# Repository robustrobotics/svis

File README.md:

# svis
This is a meta-project that contains all of the components that create a Simple Visual Inertial Synchronization approach.  The components are defined as follows.

- svis: The core algorithmic C++ library that matches camera strobe messages to camera images and gives them a common time based on the teensy clock.
- svis_ros: The ROS wrapper C++ library that handles the input and output from the core svis library.
- svis_teensy: The C and C++ code, dependencies, and utilities that build the teensy driver and allow it to be uploaded to the board.
- svis_cad: The solidworks CAD files for the svis mounting structure.
- svis_pcb: The Eagle PCB files for the svis circuit board.

### Dependencies
A list of noteable dependencies can be found below.
- catkin_tools
- Ubuntu 16.04
- ROS Kinetic
- ros-kinetic-pointgrey-camera-driver
- libusb-dev
- flycapture SDK

Use the following commands to install the required apt dependencies.
```
sudo apt install python-catkin-tools
sudo apt install ros-kinetic-pointgrey-camera-driver
sudo apt install libusb-dev
sudo apt install libc6-i386
```

Add user to dialout group.
```
sudo adduser $USER dialout
```

Use the following commands to install the flycapture SDK.
```
cd /path/to/svis/svis_ros/scripts
./install_flycapture.sh
```
Installation Steps:
- Enter sudo password: ["password", Enter]
- Confirm apt package installation: [Enter]
- Install FlyCapture2 SDK: [y, Enter]
- Add udev entry: [y, Enter]
- Enter username: ["username", Enter]
- Confirm username: [y, Enter]
- Add username to flirimaging group: [y, Enter]
- Restart udev daemon: [y, Enter] 

### Quick Start
The rough outline for running svis is as follows.  More details can be found in the individual package README files.
- Build svis and svis_ros code.
```
mkdir -p /path/to/catkin_ws/src
cd /path/to/catkin_ws/src
git clone http://github.com/jakeware/svis
cd ../
source /opt/ros/kinetic/setup.bash
catkin init
catkin config --cmake-args -DCMAKE_BUILD_TYPE=Release
catkin build
```
- Build svis_teensy code.
```
cd ./path/to/svis/svis_teensy/scripts
./build_svis_teensy.sh
```
- Install the udev rules for the teensy.
```
sudo cp /path/to/svis/svis_teensy/utilities/49-teensy.rules /etc/udev/rules.d/
```
- Upload teensy driver.  Make sure the teensy's micro USB cable is connected.  When prompted, press the program button on the teensy.
```
cd ./path/to/svis/svis_teensy/scripts
./upload_svis_teensy.sh
```
- Start the Pointgrey camera driver.
```
cd /path/to/catkin_ws
source ./devel/setup.bash
roslaunch svis_ros flea3.launch
```
- Start the svis_ros nodelet.
```
cd /path/to/catkin_ws
source ./devel/setup.bash
roslaunch svis_ros svis_ros_nodelet.launch
```

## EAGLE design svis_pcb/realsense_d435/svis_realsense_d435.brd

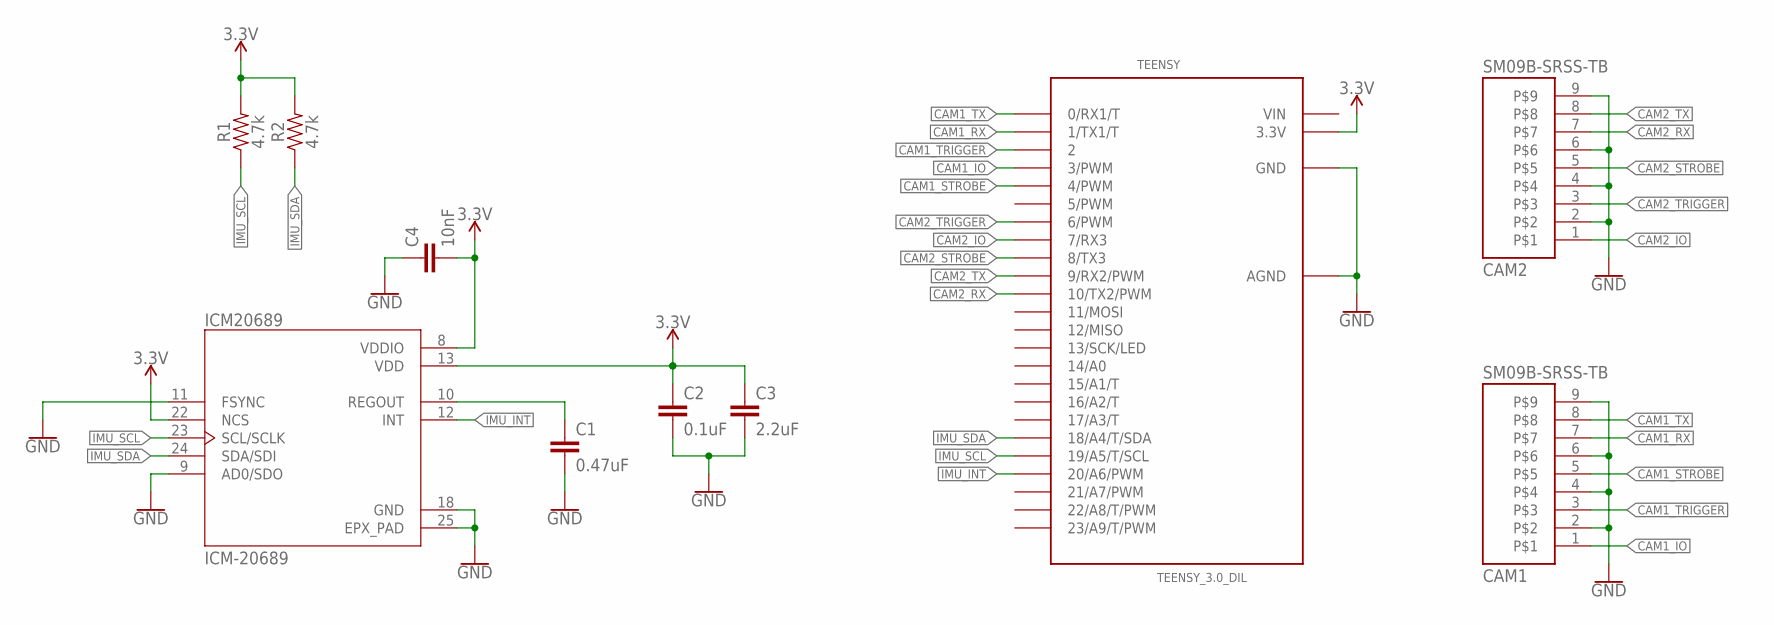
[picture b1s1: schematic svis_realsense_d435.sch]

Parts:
C1: 0.47uF; 0603
C2: 0.1uF; 0603
C3: 2.2uF; 0603
C4: 10nF; 0603
CAM1, CAM2: SM09B-SRSS-TB
ICM20689: ICM-20689; QFN50P400X400X95-25N
R1, R2: 4.7k; 0603
TEENSY: TEENSY_3.0_DIL; TEENSY_3.0-3.2&LC_DIL

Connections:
3.3V: C2.1, C3.1, C4.2, ICM20689.8 (VDDIO), ICM20689.13 (VDD), ICM20689.22 (NCS), R1.2, R2.2, TEENSY.3.3V
CAM1_IO: CAM1.1, TEENSY.3 (3/PWM)
CAM1_RX: CAM1.7, TEENSY.1 (1/TX1/T)
CAM1_STROBE: CAM1.5, TEENSY.4 (4/PWM)
CAM1_TRIGGER: CAM1.3, TEENSY.2
CAM1_TX: CAM1.8, TEENSY.0 (0/RX1/T)
CAM2_IO: CAM2.1, TEENSY.7 (7/RX3)
CAM2_RX: CAM2.7, TEENSY.10 (10/TX2/PWM)
CAM2_STROBE: CAM2.5, TEENSY.8 (8/TX3)
CAM2_TRIGGER: CAM2.3, TEENSY.6 (6/PWM)
CAM2_TX: CAM2.8, TEENSY.9 (9/RX2/PWM)
GND: C1.2, C2.2, C3.2, C4.1, CAM1.2, CAM1.4, CAM1.6, CAM1.9, CAM2.2, CAM2.4, CAM2.6, CAM2.9, ICM20689.9 (AD0/SDO), ICM20689.11 (FSYNC), ICM20689.18 (GND), ICM20689.25 (EPX_PAD), TEENSY.AGND, TEENSY.GND
IMU_INT: ICM20689.12 (INT), TEENSY.20/A6 (20/A6/PWM)
IMU_SCL: ICM20689.23 (SCL/SCLK), R1.1, TEENSY.19/A5 (19/A5/T/SCL)
IMU_SDA: ICM20689.24 (SDA/SDI), R2.1, TEENSY.18/A4 (18/A4/T/SDA)
unnamed: C1.1, ICM20689.10 (REGOUT)
VIN: TEENSY.VIN

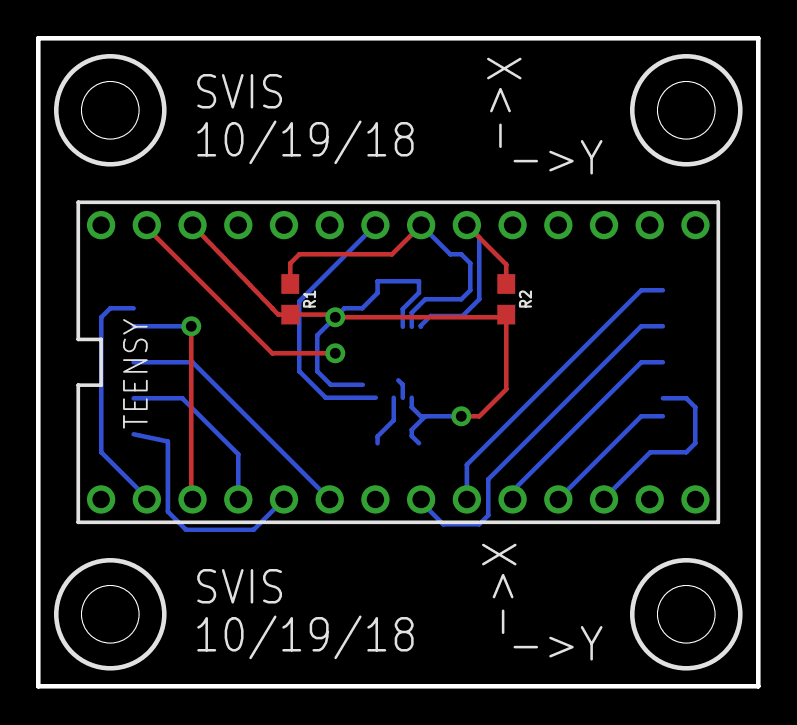
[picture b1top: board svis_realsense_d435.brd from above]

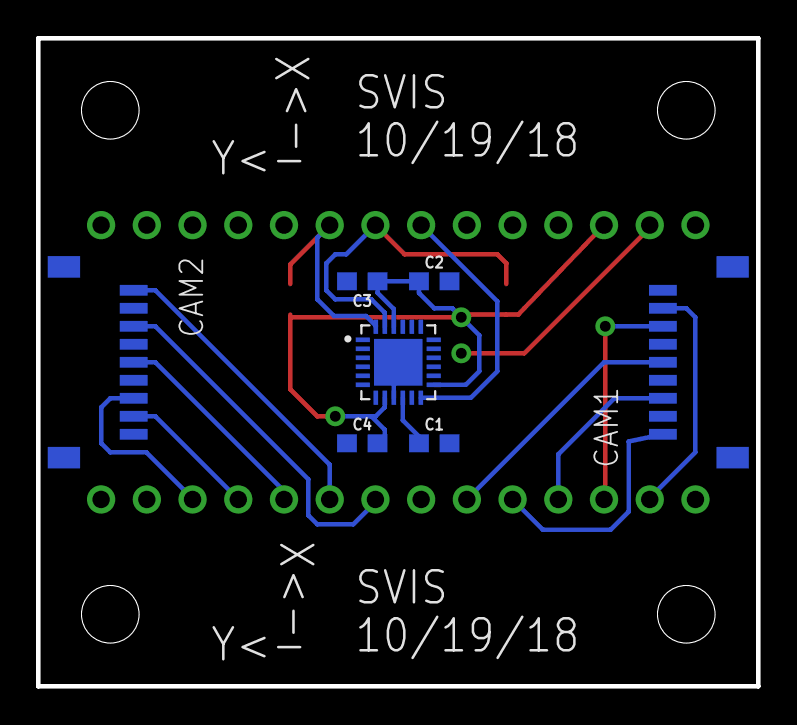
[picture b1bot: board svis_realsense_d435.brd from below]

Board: 2 copper layers, 40.0 x 36.0 mm, 10 parts (7 on the bottom side), 16 nets.

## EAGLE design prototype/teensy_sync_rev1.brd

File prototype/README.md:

# svis_cad_prototype
This package contains the CAD portion of a Simple Visual Inertial
Synchronization approach.  Due to the size of CAD files, this portion of the
project is maintained in OnShape.

* [svis_cad_prototype_mono](https://cad.onshape.com/documents/99ae2ad9c7ddd392e4e0b58d/w/969cc026d4e8d11d2a2540fa/e/534a900b9d68d548818dfd7e)
* [svis_cad_prototype_stereo](https://cad.onshape.com/documents/c2e3b5391432601dd5a34811/w/07971ed09aed7bb4962e395a/e/211f444c45c3098888544dae)

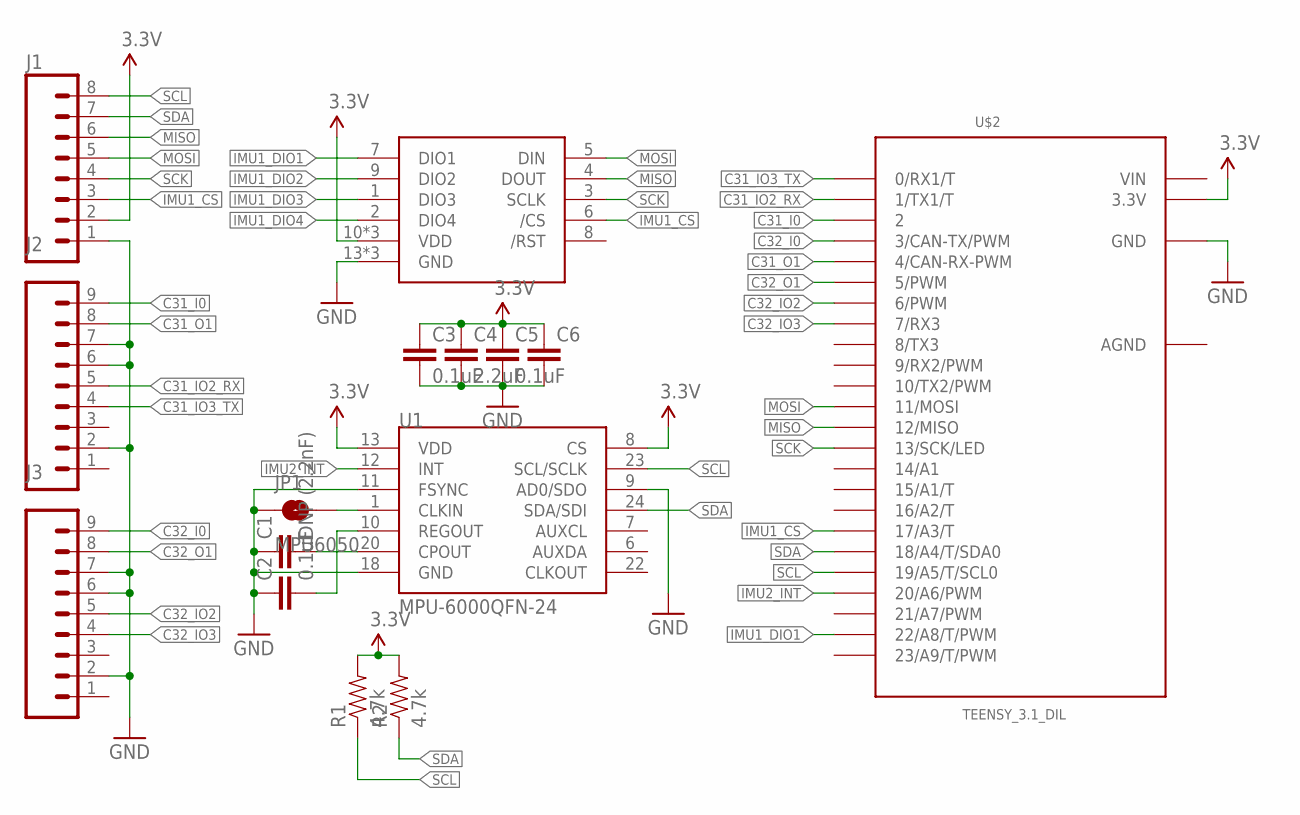
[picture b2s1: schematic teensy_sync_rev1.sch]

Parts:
C1: DNP (2.2nF); 0402-CAP
C2, C3, C5: 0.1uF; 0402-CAP
C4: 2.2uF; 0402-CAP
C6: CAP0402-CAP; 0402-CAP
J1: M08; 1X08_ROUND
J2, J3: M09; 1X09
JP1: MPU6050; PAD-JUMPER-2-NO_YES_SILK
R1, R2: 4.7k; 0603-RES
U1: MPU-6000QFN-24; QFN-24-TESTING
U$1: ADIS16448
U$2: TEENSY_3.1_DIL; TEENSY3-DIL

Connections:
3.3V: C3.1, C4.1, C5.1, C6.1, J1.2, R1.2, R2.2, U1.8 (CS), U1.13 (VDD), U$1.10 (VDD), U$1.11 (VDD), U$1.12 (VDD), U$2.3.3V
AGND: U$2.AGND
C31_I0: J2.9, U$2.2
C31_IO2_RX: J2.5, U$2.1 (1/TX1/T)
C31_IO3_TX: J2.4, U$2.0 (0/RX1/T)
C31_O1: J2.8, U$2.4 (4/CAN-RX-PWM)
C32_I0: J3.9, U$2.3 (3/CAN-TX/PWM)
C32_IO2: J3.5, U$2.6 (6/PWM)
C32_IO3: J3.4, U$2.7 (7/RX3)
C32_O1: J3.8, U$2.5 (5/PWM)
GND: C1.1, C2.1, C3.2, C4.2, C5.2, C6.2, J1.1, J2.2, J2.6, J2.7, J3.2, J3.6, J3.7, JP1.1, U1.9 (AD0/SDO), U1.11 (FSYNC), U1.18 (GND), U$1.13 (GND), U$1.14 (GND), U$1.15 (GND), U$2.GND
IMU1_CS: J1.3, U$1.6 (/CS), U$2.17/A3 (17/A3/T)
IMU1_DIO1: U$1.7 (DIO1), U$2.22/A8 (22/A8/T/PWM)
IMU1_DIO2: U$1.9 (DIO2)
IMU1_DIO3: U$1.1 (DIO3)
IMU1_DIO4: U$1.2 (DIO4)
IMU2_INT: U1.12 (INT), U$2.20/A6 (20/A6/PWM)
MISO: J1.6, U$1.4 (DOUT), U$2.12 (12/MISO)
MOSI: J1.5, U$1.5 (DIN), U$2.11 (11/MOSI)
unnamed: C1.2, U1.20 (CPOUT)
unnamed: JP1.2, U1.1 (CLKIN)
REGOUT: C2.2, U1.10 (REGOUT)
SCK: J1.4, U$1.3 (SCLK), U$2.13 (13/SCK/LED)
SCL: J1.8, R1.1, U1.23 (SCL/SCLK), U$2.19/A5 (19/A5/T/SCL0)
SDA: J1.7, R2.1, U1.24 (SDA/SDI), U$2.18/A4 (18/A4/T/SDA0)
VIN: U$2.VIN

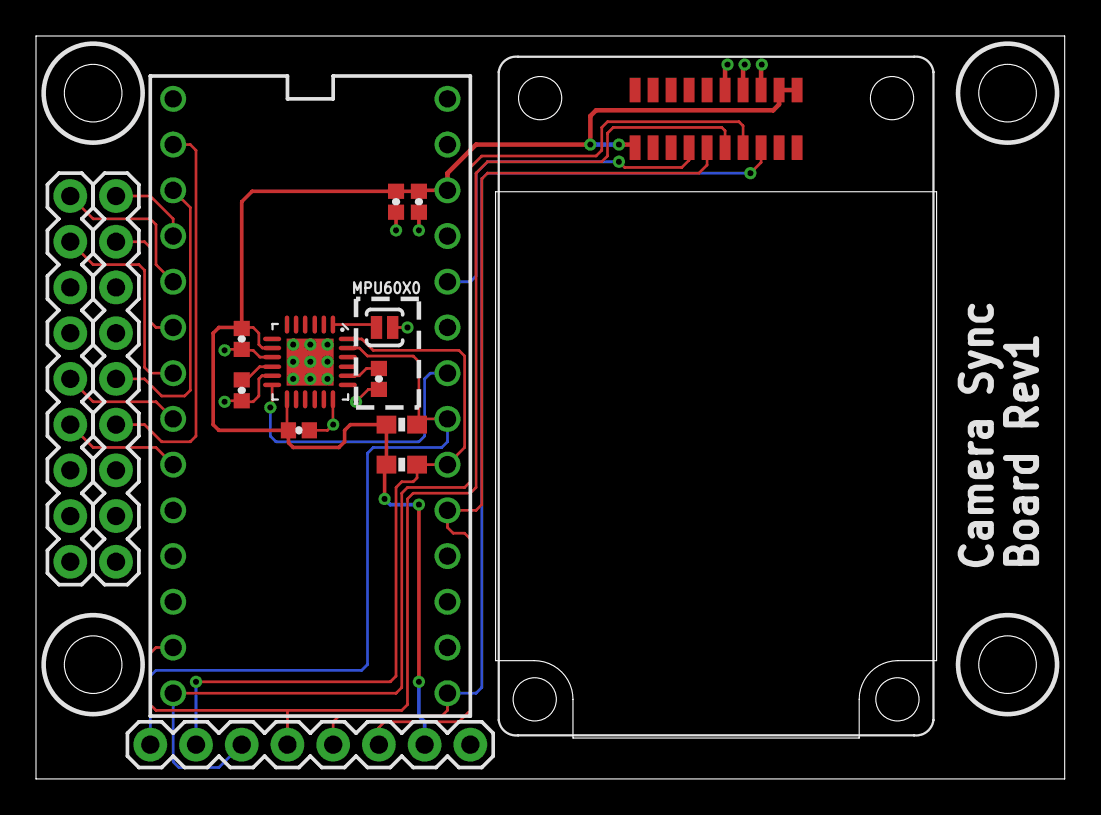
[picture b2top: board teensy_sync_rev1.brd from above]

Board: 2 copper layers, 57.1 x 41.3 mm, 15 parts (0 on the bottom side), 21 nets.

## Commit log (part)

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2016-12-23 Switch upload command to CLI.
2016-12-23 Remove ARDUINO_HOME.
2016-12-23 Remove TEENSY3_OVERRIDE_FILES.
2016-12-23 Add comment blocks for separation.
2016-12-23 Remove M_LAYOUT.
2016-12-23 Remove check for linker definitions override.
2016-12-23 Remove M_TEENSY_VERSION and M_BOARD.
2016-12-23 Move PROJECT_PATH variable.
2016-12-23 Remove unused make targets.
2016-12-23 Change OUT_PATH to BIN_PATH.
2016-12-23 Add build folder.
2016-12-23 Remove LICENSE.txt.
2016-12-23 Move bin into build folder.
2016-12-23 Remove original blink example.
2016-12-23 Rename and cleanup new blink example.
2016-12-23 Rename blink project target.
2016-12-24 Working hello_world example.
2016-12-24 Update usb_raw_hid structure.
2016-12-24 Add cores folder and move teensy3.
2016-12-24 Add missing cores folders
2016-12-24 Remove usb libraries in tools.
2016-12-24 Rename tools to utilities.
2016-12-25 Reworking blink. Currently broken.
2016-12-25 Add initial cmake files.
2016-12-26 Comment out CMAKE_TOOLCHAIN_FILE.
    This variable does not exist in cmake 2.8.
2016-12-26 Switch TOOLCHAIN_ROOT to TOOLCHAIN_PREFIX.
2016-12-26 Remove TOOL_OS_SUFFIX.
2016-12-26 Update paths and variables.
2016-12-26 Remove unnecessary quotes from definitions.
2016-12-26 Remove CACHE STRING and comment.
2016-12-26 Unset CMAKE_SHARED_LIBRARY_LINK variables.
2016-12-26 Remove debugging work.
2016-12-26 Cleanup CMakeLists.
2016-12-26 Remove redundant mk20dx256.ld.
2016-12-26 Update TEENSYDUINO_VERSION in blink Makefile.
2016-12-26 Remove usb dependency files accidentally added in previous commit.
2016-12-27 Remove examples CMakeLists.
2016-12-27 Add TODO for cmake includes.
2016-12-27 Remove TyQt references.
2016-12-27 Use GLOB for teensy core.
2016-12-27 Add prints for blink Makefile build.
2016-12-27 Update compile and link flags.
2016-12-27 Remove Blink.pde.
2016-12-28 Remove usb_api.h from usb_raw_hid example.
2016-12-28 Remove blink Makefile.
2016-12-28 Remove usb_raw_hid Makefile.
2016-12-28 Add project specific CMakeLists files.
2016-12-28 Set TEENSY_FREQUENCY to 48MHz.
2016-12-28 Switch to using project specific CMakeLists.
2016-12-28 Fix C_CORE GLOB typo.
2016-12-28 Remove USB_MODE and FREQUENCY from default defs.
2016-12-28 Remove empty CMakeLists.
2016-12-28 Move everything up a level for svis_teensy change.
2016-12-30 Rough README.
2016-12-30 Add partial code to automatically parse version numbers.
2016-12-31 Add attach_interrupt example.
2017-01-01 Add adafruit_9dof example.
2017-01-07 Add MPU6050 library.
2017-01-07 Add mpu6050_raw example.
2017-01-19 Initial working IMU callbacks.
2017-01-19 Single imu read function at 1kHz.
2017-01-19 Cleanup.
2017-01-19 Rough out strobe and imu implementation.
2017-01-20 Decrease imu interrupt for debugging.
2017-01-20 Switch back to SERIAL for debugging.
2017-01-20 Comment out HID send.
2017-01-20 Add checks for count and tail.
2017-01-20 Cleanup setup function.
2017-01-20 Add led blink and cleanup.
2017-01-20 Modify blinking.
2017-01-20 Add debug prints and PrintSendBuffer..
2017-01-20 Add strobe_count and cleanup.
2017-01-20 Remove debug prints.
2017-01-21 Add initial files.
2017-01-21 Add initial hid files.
2017-01-21 Remove hid Makefile.
2017-01-21 Rename hid_LINUX.c.
2017-01-21 Cleanup and rename.
2017-01-21 Initial launch file.
2017-01-22 Fixed usb linking error.
2017-01-22 Switch to RAWHID.
2017-01-22 Remove rawhid send prints.
2017-01-22 Add packet counts.
2017-01-22 Disable CMAKE_VERBOSE_MAKEFILE.
2017-01-22 Add #defines for sizes.
2017-01-23 Refactor to use fixed packet structure.
2017-01-23 Initial refactor to use fixed packet structure.
2017-01-23 Add checksum and replace defines with constants.
2017-01-23 Partial cleanup.
2017-01-23 Added initial version of board schematic and layout.
2017-01-23 Add send_errors.
2017-01-24 Move struct definitions.
2017-01-24 Switch to std::vector for buffer.
2017-01-24 Add TestPushIMU and TestPushStrobe.
2017-01-24 Fix imu_data_buffer indexing.
2017-01-24 Added ICM20689.h to replace MPU6050.h
2017-01-24 Remove unused files.
2017-01-24 Copy MPU6050 for base of ICM20689.
2017-01-24 Updated library.json to ICM20689 version. Modified from MPU6050 version.
2017-01-24 Cleaned up ICM20689.h. Commented out any unimplemented functions for first test.
2017-01-25 Updated brd and sch file to reflect prototype boards ordered.
2017-01-25 Add image callback and debug.
2017-01-25 Added BOM for prototype PCB.
2017-01-26 Add debug messages.
2017-01-26 Add imu low-pass filter.
2017-01-31 White space cleanup.
2017-01-31 Add path to hid.h include.
2017-01-31 Remove dt print statement.
2017-01-31 Start rough time offset implementation.
2017-02-01 Update struct names.
2017-02-02 Rework timestamps.
2017-02-02 Fix time_offset calculation and variable types.
2017-02-02 Do not force strobe_count rollover.
2017-02-02 Rename image pub and sub.
2017-02-02 Add raw strobe and imu ros messages for debug.
2017-02-02 Define STROBE_PIN and add INPUT_PULLUP option.
    Not that the pullup resistor on the teensy is too high to be useful.
2017-02-02 Switch from RISING to FALLING on strobe interrupt.
    This is to match the default ROS driver configuration.
2017-02-02 Change print statement for no data case.
2017-02-02 Add raw publishers and Push functions.
2017-02-02 Add ImageMetadata class.
2017-02-03 Add rough sync function.
2017-02-03 Cleanup and add GetCountOffset().
2017-02-03 Organize member variables.
2017-02-03 Cleanup and initialize all member variables.
2017-02-04 Move spinOnce() to top of loop.
2017-02-04 Fix strobe_count_total bug.
2017-02-04 Add iterator loops to AssociateStrobe.
    Also remove strobe and camera packets once matched.
2017-02-04 Dirty hack to get around ConstPtr camera message.
    Couldn't figure out a way to modify the timestamp on the ConstPtr
    messages Image and CameraInfo messages.
2017-02-06 Add Image callback. Currently segfaulting.
2017-02-06 Debugging...
2017-02-07 Add PrintStrobeBuffer.
2017-02-07 Rollover fix. Fuck that. Seriously.
2017-02-07 Add raw strobe count to PrintStrobeBuffer.
2017-02-07 Add timing.
2017-02-07 Copy camera image and info message.
2017-02-07 Cleanup print statements.
2017-02-07 Add links to prototype files.
2017-02-07 Add initial versions of repos.
2017-02-08 Switch to ICM20689.
2017-02-08 Fix mpu6050/icm20689 mixup.
2017-02-09 Fix trigger timing.
2017-02-09 Add configuration packet and startup led blinks.
2017-02-09 Add configuration packet.
2017-02-09 Remove ros submodule.
2017-02-09 Remove pcb submodule.
2017-02-09 Remove svis prefix from folders.
2017-02-09 Add warning for missing camera messages.
2017-02-09 Reorganize GetStrobeTotal.
2017-02-09 Add reset function.
2017-02-09 Update led user feedback blink functions.
2017-02-09 Fix setup header typo.
2017-02-09 Cleanup SIGINT warning text.
2017-02-10 Add SendSetup().
2017-02-10 Add warnings when buffers are at max size.
2017-02-10 Comment out rollover warning.
2017-02-13 Correct param yaml name.
2017-02-14 Cleanup launch file comments.
2017-02-14 Move params out of node to fix namespace issue.
2017-02-14 Add acc and gyro sensitivity params.
2017-02-14 Rearrange teensy blink functions.
2017-02-14 Add ResetParams function.
2017-02-14 Move gyro and acc range select assignment.
2017-02-14 Add accel and gyro range select and correction to ros.
2017-02-14 Convert accelerations into m/s.
2017-02-14 Fix AFS_SEL reference table.
2017-02-14 Move param load to fix namespace issue again.
2017-02-28 Revert lp_win_size to imu_filter_size.
2017-02-28 Add rad_per_deg constant.
2017-02-28 Add acc_raw and gyro_raw variables to ImuPacket.
2017-02-28 Publish converted Imu messages.
2017-02-28 Switch to static_cast.
2017-02-28 Fix gyro and accel range comment.
2017-02-28 Switch loops to use size() for max value.
2017-02-28 Update FilterImu to use floats and new format.
2017-02-28 Add check for camera trigger reconfigure step.
2017-02-28 Add dynamic_reconfigure step for camera trigger.
2017-03-01 Make camera_frame an arg.
2017-07-07 Add udev rules.
2017-07-07 Reduce camera rate to 30 Hz to avoid rate bug.
2017-07-07 Add camera driver warning.
2017-07-07 Switch to using camera and strobe pairs.
2017-07-07 Formatting.
2017-07-07 Add trigger pulse packets.
    Builds but is still untested.
2017-07-07 Add buffer size prints.
2017-07-07 Fix buffer size bug.
2017-08-30 Move data structs and classes into their own headers.
2017-08-30 Move implementation from nodelet into ros wrapper.
2017-08-30 Move data structs and classes to svis.
2017-08-31 Add svis library and start refactor.
2017-08-31 Add svis object back into svis_ros.
2017-08-31 Cleanup timing stuff.
2017-08-31 Pass buffers to Push functions.
2017-08-31 Cleanup Update function.
2017-08-31 Add constructor.
2017-08-31 Always pass buffers.
2017-08-31 Add num return to ReadHID.
2017-08-31 Timing cleanup and add private members to svis.
2017-08-31 More timing cleanup.
2017-08-31 Add PublishTiming place holder.
2017-08-31 Add new lines to printf statements.
2017-09-04 Remove svis_ros dependency of svis_ros_nodelet.
2017-09-04 Remove public declaration in CameraStrobePacket struct.
2017-09-05 Switch to std::size_t.
2017-09-05 Reorganize headers.
2017-09-05 Make publishers const, except for camera pub.
2017-09-06 Add custom messages.
2017-09-06 Add semicolon after struct definitions.
2017-09-06 Fix timestamp_ros_rx initialization typo.
2017-09-06 Switch to std::memcpy.
2017-09-06 Comment out PrintImageQuadlet and PrintMetaDataRaw.
2017-09-06 Add svis_ros back to nodelet dependency.
    Removing this caused runtime errors with undefined symbols.
2017-09-06 Add msg conversion functions.
2017-09-06 Switch to std::array in camera_info.h.
2017-09-06 Add TimeNow std::function to svis.
2017-09-06 Remove stamp struct from header and switch to double.
2017-09-07 Remove svis from ros wrapper build and add as cmake dependency.
2017-09-07 Add svis cmake library.
2017-09-07 Rename folders.
2017-09-08 Fixed libusb build issue. Includes extra debugging code.
2017-09-10 Hardcode svis library path. This works.
2017-09-11 Remove svis_INCLUDE_DIRS and svis_LIBRARIES prints.
2017-09-11 Remove unnecessary compile and linker flags.
2017-09-11 Cleanup cmake.in.
2017-09-11 Fix sloppy memory leak.
2017-09-12 Set pulse_trigger on restart. Seems to work now.
2017-09-14 Add CMSIS DSP math library.
2017-09-14 Upload documentation and cleanup cmake.
2017-09-14 Remove .gitmodules file.
2017-09-19 Cleanup README.
2017-09-19 Update README.
2017-09-19 Uncomment gcc-arm wget.
2017-09-22 First round of build fixes.
2017-09-29 Add install_flycapture script.
2017-10-14 Update shutter speed and add flea3 calibration.
2018-07-03 Add libc6-i386 dependency.
2018-07-03 Add user to dialout.
2018-07-05 Do not cast timestamp_teensy as an int after averaging.
2018-07-06 Add DecimateImu.
2018-07-06 Add artificial time offset.
2018-07-09 Fix circular buffer interaction in DecimateImu.
2018-07-11 Cleanup flea3 launch file and enable auto exposure.
2018-07-11 Revert imu_pubs change.
2018-07-11 Update FilterImu.
2018-07-18 Remove imu_stamp_buffer.
2018-07-18 Use hid packet timestamp for time_offset.
2018-07-18 Handle strobe before filtering imu.
2018-07-19 Switch to strobe input on teensy.
2018-07-24 Add input topic params and strip out old subs and pubs.
2018-07-25 Add yaml driven input topics.
2018-07-25 Add CameraSynchronizer.
2018-07-27 Add missing header to CMakeLists.
2018-07-27 Switch CameraPacket to struct.
2018-07-27 Add max_buffer_size to camera_synchronizer constructor.
2018-07-30 Build sync'd messages.
2018-07-31 First time publishing synchronized outputs.
2018-08-24 Add count_total to strobe message and a few print statements.
2018-08-24 Fix synchronization bug.
2018-08-24 Remove time_offset print.
2018-08-27 Do not compute offset for last sample.
2018-08-27 Fix offsets size bug.
2018-08-27 Subtract half of exposure time.
2018-09-11 First commit of realsense_d435_pcb.
2018-09-12 Adding libraries and packages.
2018-09-20 Changes for launch and gcc on quad.
2018-09-25 First cut at complete board.
2018-10-01 Add design rule files.
2018-10-01 Update design to pass DRC and ERC.
2018-10-02 First hover flight with 5 second sleep.
2018-10-12 Remove stray trace.

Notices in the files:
parts and their libraries:
SparkFun-Sensors: Licensing: Creative Commons ShareAlike 4.0 International - https://creativecommons.org/licenses/by-sa/4.0
